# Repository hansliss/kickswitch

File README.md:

# kickswitch
Kickstart switcher for Amiga 2000

A switch for cramming 6 Kickstart images of different size into a single EPROM and make them switchable.

Switching is done by triggering a RESET low signal for at least two seconds, which can be done
from the keyboard by holding down CTRL-Amiga-Amiga.

Note that for some models of A500, you may need pullups on the address lines:
http://bax.comlab.uni-rostock.de/en/hardware/amiga500/kickstart-eprom/

A jumper is provided to select between pin 1 or 31 for A17 - older A2000 and A500 models
used the wrong pin for this.

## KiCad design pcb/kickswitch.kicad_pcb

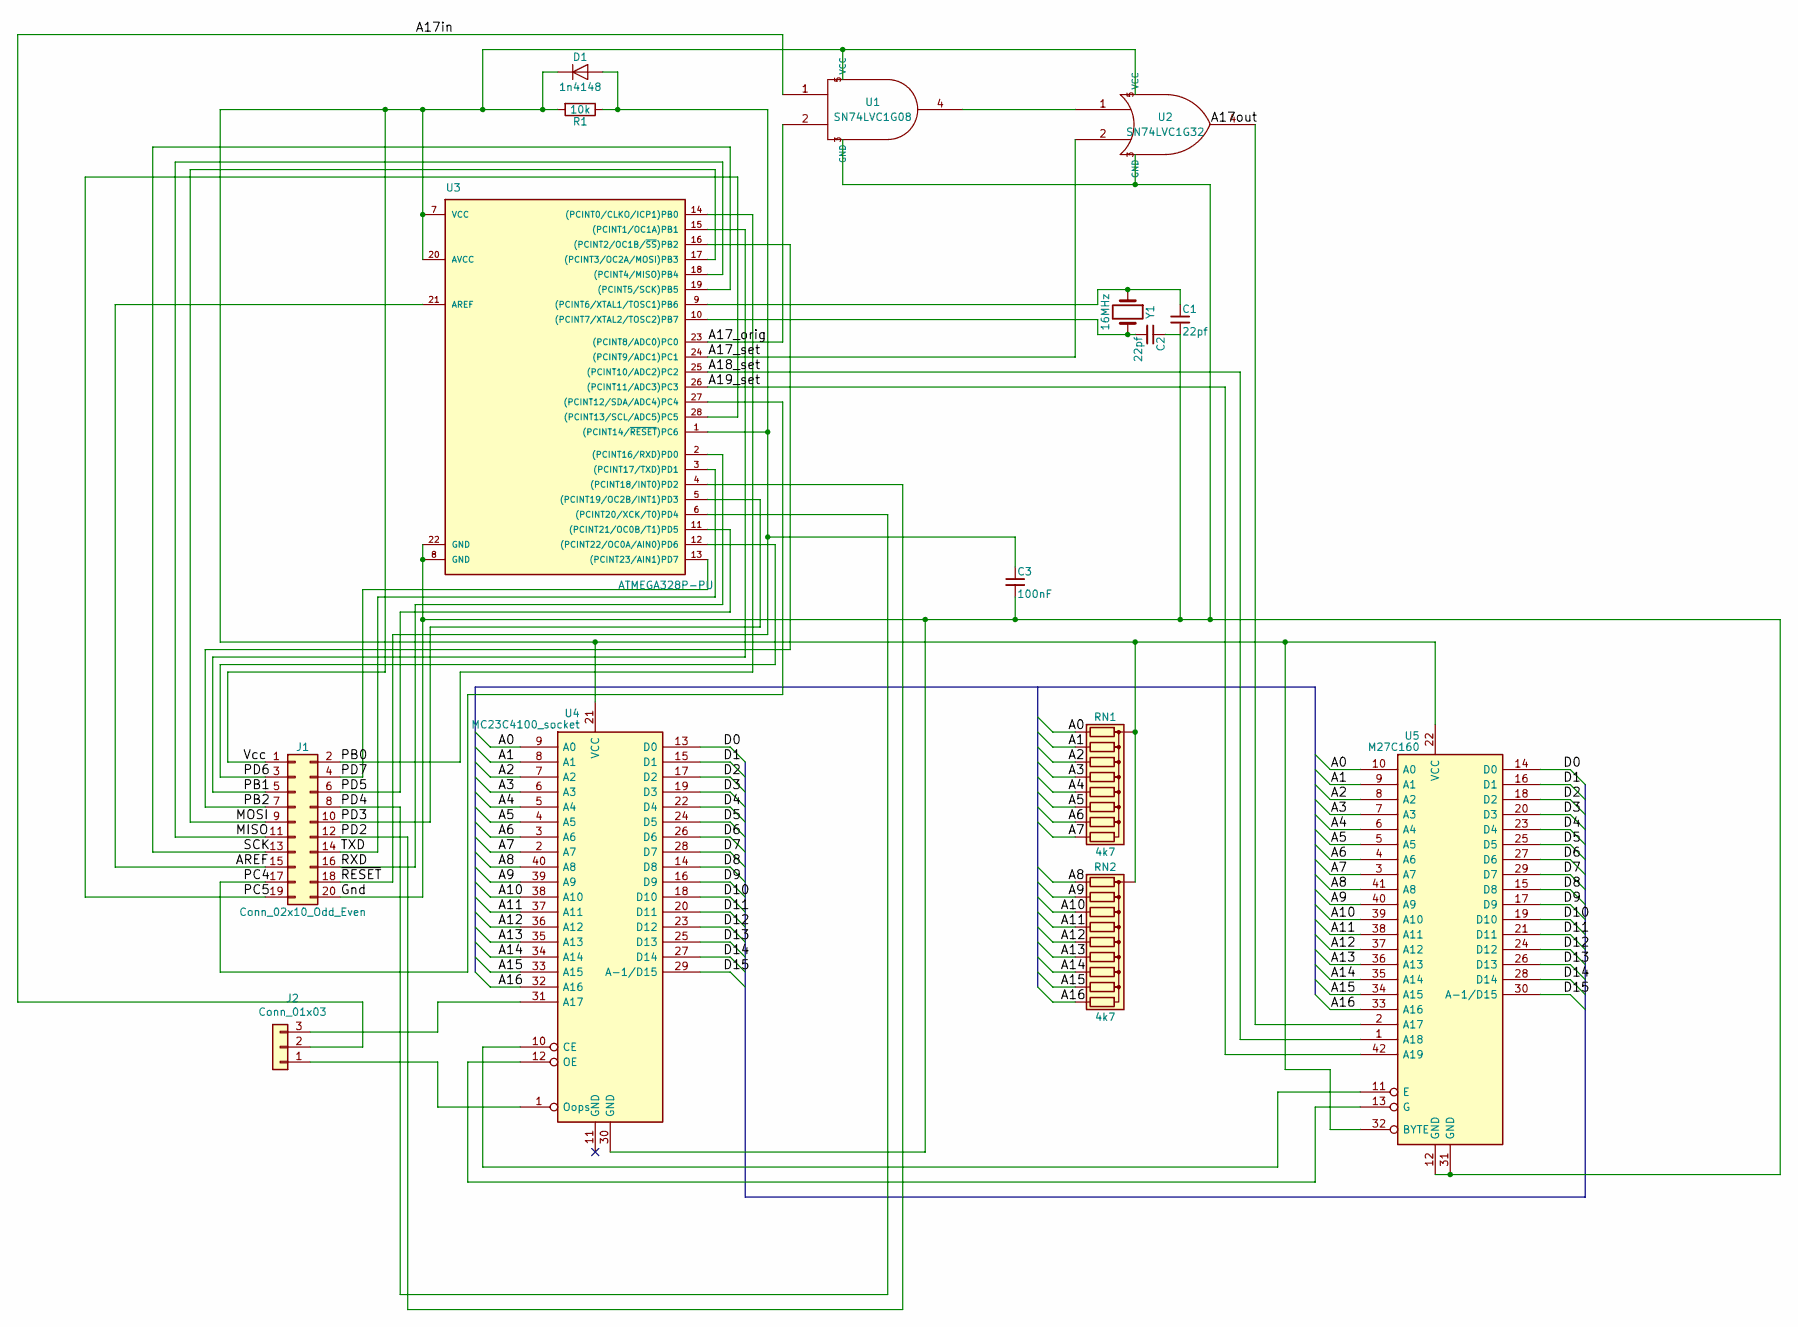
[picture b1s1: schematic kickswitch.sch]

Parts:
C1, C2: 22pf; C_0603
C3: 100nF; C_0603
D1: 1n4148; D_SOD-123F
J1: Conn_02x10_Odd_Even; Pin_Header_Straight_2x10_Pitch2.54mm
J2: Conn_01x03; Pin_Header_Straight_1x03_Pitch2.54mm
R1: 10k; R_0603
RN1: 4k7; R_Array_SIP9
RN2: 4k7; R_Array_SIP10
U1: SN74LVC1G08; SOT-23-5
U2: SN74LVC1G32; SOT-23-5
U3: ATMEGA328P-PU; DIP-28_W7.62mm
U4: MC23C4100_socket; DIP-40_W15.24mm_Socket
U5: M27C160; DIP-42_W15.24mm_Socket
Y1: 16MHz; Crystal_HC49-4H_Vertical

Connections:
/A0: RN1.2 (R1), U4.9 (A0), U5.10 (A0)
/A1: RN1.3 (R2), U4.8 (A1), U5.9 (A1)
/A2: RN1.4 (R3), U4.7 (A2), U5.8 (A2)
/A3: RN1.5 (R4), U4.6 (A3), U5.7 (A3)
/A4: RN1.6 (R5), U4.5 (A4), U5.6 (A4)
/A5: RN1.7 (R6), U4.4 (A5), U5.5 (A5)
/A6: RN1.8 (R7), U4.3 (A6), U5.4 (A6)
/A7: RN1.9 (R8), U4.2 (A7), U5.3 (A7)
/A8: RN2.2 (R1), U4.40 (A8), U5.41 (A8)
/A9: RN2.3 (R2), U4.39 (A9), U5.40 (A9)
/A10: RN2.4 (R3), U4.38 (A10), U5.39 (A10)
/A11: RN2.5 (R4), U4.37 (A11), U5.38 (A11)
/A12: RN2.6 (R5), U4.36 (A12), U5.37 (A12)
/A13: RN2.7 (R6), U4.35 (A13), U5.36 (A13)
/A14: RN2.8 (R7), U4.34 (A14), U5.35 (A14)
/A15: RN2.9 (R8), U4.33 (A15), U5.34 (A15)
/A16: RN2.10 (R9), U4.32 (A16), U5.33 (A16)
/A17_orig: U1.2, U3.23 ((PCINT8/ADC0)PC0)
/A17_set: U2.2, U3.24 ((PCINT9/ADC1)PC1)
/A17in: J2.2, U1.1
/A18_set: U3.25 ((PCINT10/ADC2)PC2), U5.1 (A18)
/A19_set: U3.26 ((PCINT11/ADC3)PC3), U5.42 (A19)
/AREF: J1.15, U3.21 (AREF)
/D0: U4.13 (D0), U5.14 (D0)
/D1: U4.15 (D1), U5.16 (D1)
/D2: U4.17 (D2), U5.18 (D2)
/D3: U4.19 (D3), U5.20 (D3)
/D4: U4.22 (D4), U5.23 (D4)
/D5: U4.24 (D5), U5.25 (D5)
/D6: U4.26 (D6), U5.27 (D6)
/D7: U4.28 (D7), U5.29 (D7)
/D8: U4.14 (D8), U5.15 (D8)
/D9: U4.16 (D9), U5.17 (D9)
/D10: U4.18 (D10), U5.19 (D10)
/D11: U4.20 (D11), U5.21 (D11)
/D12: U4.23 (D12), U5.24 (D12)
/D13: U4.25 (D13), U5.26 (D13)
/D14: U4.27 (D14), U5.28 (D14)
/D15: U4.29 (A-1/D15), U5.30 (A-1/D15)
/Gnd: C1.2, C2.1, C3.2, J1.20, U1.3 (GND), U2.3 (GND), U3.8 (GND), U3.22 (GND), U4.30 (GND), U5.12 (GND), U5.31 (GND)
/MISO: J1.11, U3.18 ((PCINT4/MISO)PB4)
/MOSI: J1.9, U3.17 ((PCINT3/OC2A/MOSI)PB3)
/PB0: J1.2, U3.14 ((PCINT0/CLKO/ICP1)PB0)
/PB1: J1.5, U3.15 ((PCINT1/OC1A)PB1)
/PB2: J1.7, U3.16 ((PCINT2/OC1B/~SS~)PB2)
/PC4: J1.17, U3.27 ((PCINT12/SDA/ADC4)PC4)
/PC5: J1.19, U3.28 ((PCINT13/SCL/ADC5)PC5)
/PD2: J1.12, U3.4 ((PCINT18/INT0)PD2)
/PD3: J1.10, U3.5 ((PCINT19/OC2B/INT1)PD3)
/PD4: J1.8, U3.6 ((PCINT20/XCK/T0)PD4)
/PD5: J1.6, U3.11 ((PCINT21/OC0B/T1)PD5)
/PD6: J1.3, U3.12 ((PCINT22/OC0A/AIN0)PD6)
/PD7: J1.4, U3.13 ((PCINT23/AIN1)PD7)
/RXD: J1.16, U3.2 ((PCINT16/RXD)PD0)
/SCK: J1.13, U3.19 ((PCINT5/SCK)PB5)
/TXD: J1.14, U3.3 ((PCINT17/TXD)PD1)
/Vcc: D1.1 (K), J1.1, R1.2, RN1.1 (common), RN2.1 (common), U1.5 (VCC), U2.5 (VCC), U3.7 (VCC), U3.20 (AVCC), U4.21 (VCC), U5.22 (VCC), U5.32 (BYTE)
/~RESET: C3.1, D1.2 (A), J1.18, R1.1, U3.1 ((PCINT14/~RESET~)PC6)
unnamed: C1.1, U3.9 ((PCINT6/XTAL1/TOSC1)PB6), Y1.1
unnamed: C2.2, U3.10 ((PCINT7/XTAL2/TOSC2)PB7), Y1.2
unnamed: J2.1, U4.1 (Oops)
unnamed: J2.3, U4.31 (A17)
unnamed: U1.4, U2.1
unnamed: U2.4, U5.2 (A17)
unnamed: U4.10 (CE), U5.11 (E)
unnamed: U4.12 (OE), U5.13 (G)

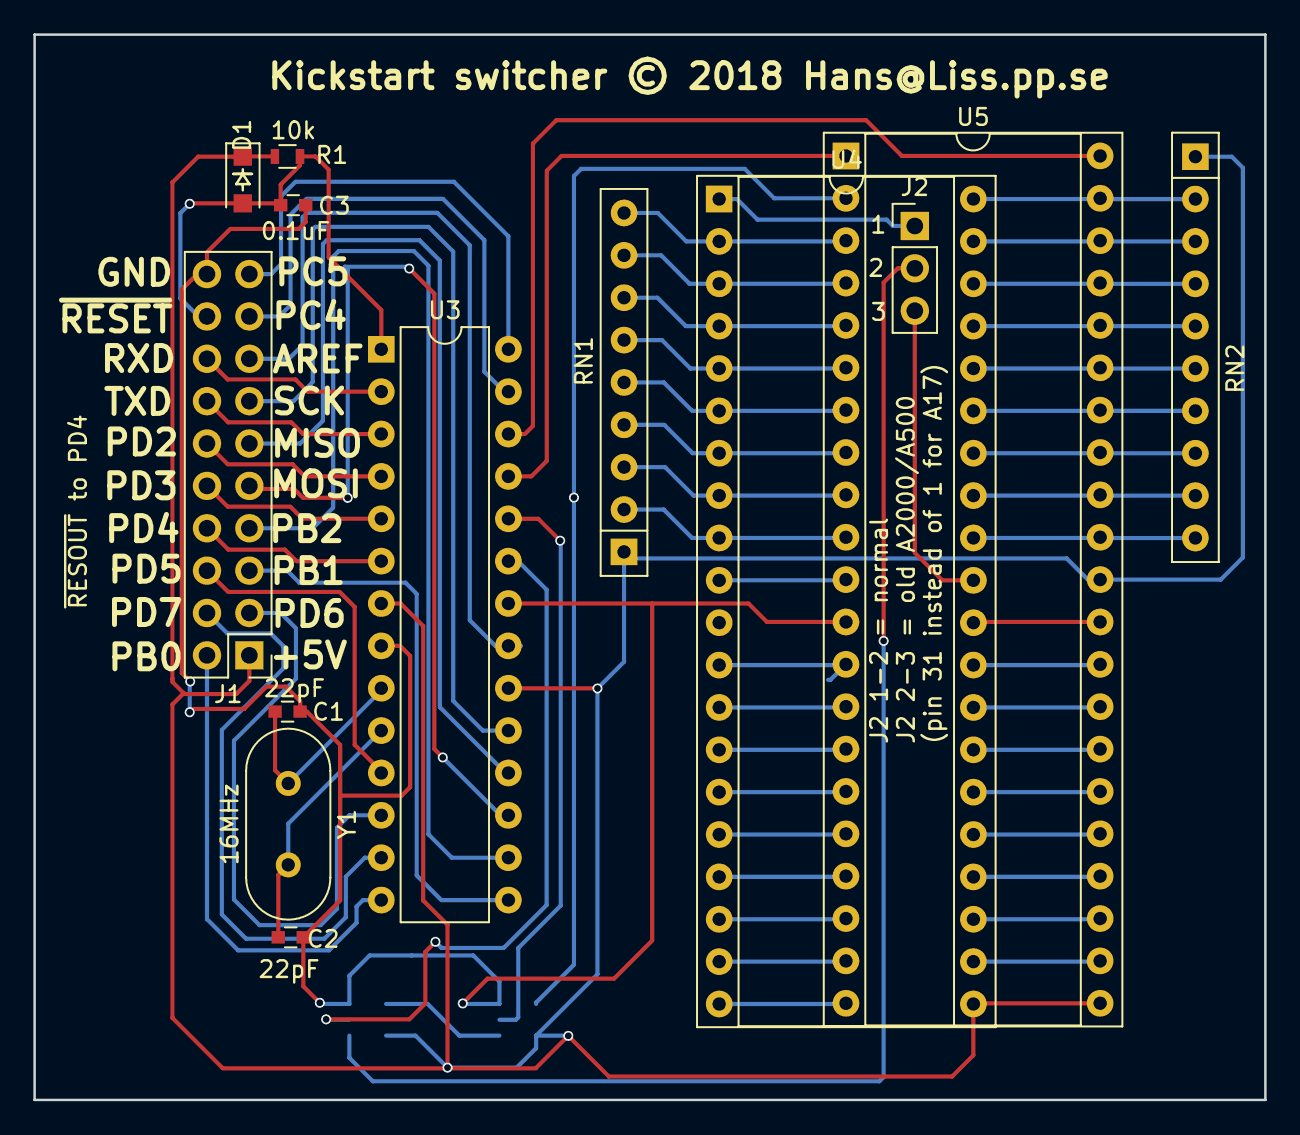
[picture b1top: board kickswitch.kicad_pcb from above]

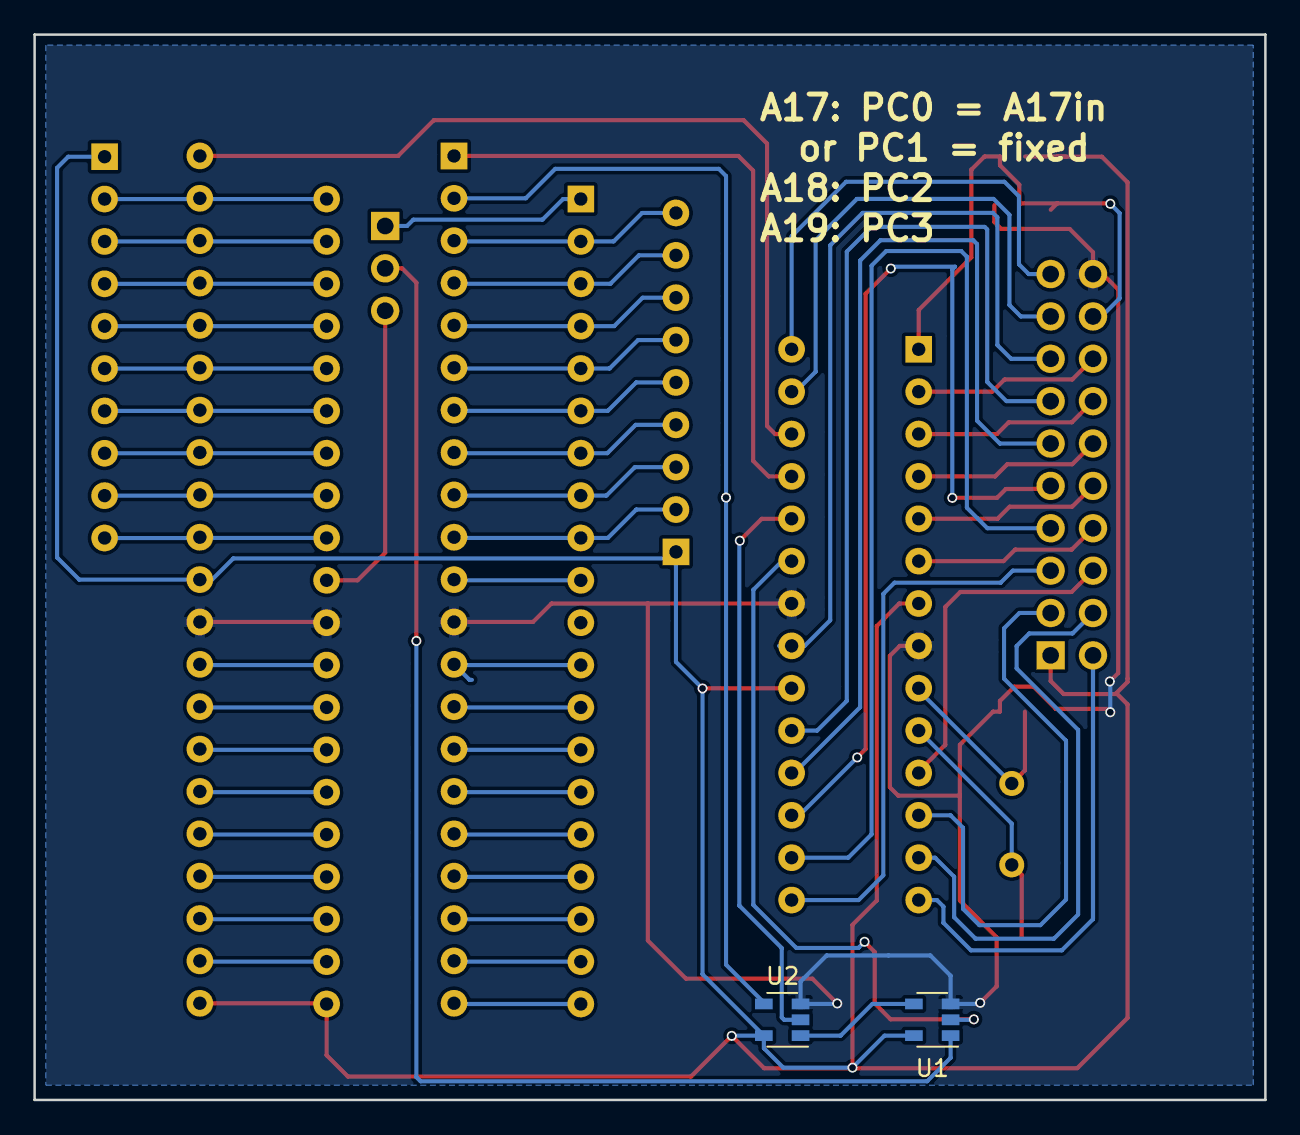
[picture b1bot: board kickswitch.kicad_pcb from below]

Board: 2 copper layers, 73.8 x 63.9 mm, 15 parts (2 on the bottom side), 66 nets.

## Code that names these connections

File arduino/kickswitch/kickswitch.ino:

/*
 * Kickswitch code
 * Produce adressing signals to a banked Kickstart ROM for A17 to A19 on PC0, PC1, PC2 and PC3 based on a selected value.
 * The value can be changed by holding a signal low for at least two seconds. This is intended to be taken from the
 * /RSTOUT signal on the parallel port on the Amiga, which will make it possible to switch between different Kickstart
 * versions by holding down CTRL-Amiga-Amiga for two seconds.
 * With six Kickstart images in a single ROM, the first four 128kW, and the last two 256kW, we need to be able to either
 * ignore the original A17 (for the first four) or use it (for the last two). The circuit will allow us to use PC0 to pass
 * through the original A17 to the ROM, or leave that off and use PC1 to set it HIGH/LOW. A18 and A19 are controlled by
 * PC2 and PC3, respectively. So we use a simple switch statement and set the appropriate values whenever the switch changes.
 */

#include <EEPROM.h>

#define RSTPin 4

int pc0 = 14;
int pc1 = 15;
int pc2 = 16;
int pc3 = 17;

int pinsByVal[] = {0x00, 0x02, 0x04, 0x06, 0x09, 0x0D};

int v;
int oldv;
int RSTState=HIGH;

void setup() {
  pinMode(pc0, OUTPUT);
  pinMode(pc1, OUTPUT);
  pinMode(pc2, OUTPUT);
  pinMode(pc3, OUTPUT);
  pinMode(RSTPin, INPUT_PULLUP);
  oldv = -1;
  v = EEPROM.read(0);
#ifdef SERIAL
  Serial.begin(9600);
#endif
}

long ResetMillis=-1;

void loop() {
  int curRSTState = digitalRead(RSTPin);
  if (curRSTState != RSTState) {
    if (curRSTState == LOW) {
      ResetMillis = millis();
    }
    RSTState = curRSTState;
  }
  if (RSTState == LOW && ResetMillis != -1) {
    long elapsed = millis() - ResetMillis;
    if (elapsed >= 2000) {
      v = (v + 1) % 6;
      ResetMillis = -1;
    }
  }
  if (v != oldv && RSTState == LOW) {
#ifdef SERIAL
    Serial.println(String(v) + ": " + String(pinsByVal[v]));
#endif
    oldv = v;
    EEPROM.write(0, v);
    digitalWrite(pc0, (pinsByVal[v] & 0x01)?HIGH:LOW);
    digitalWrite(pc1, (pinsByVal[v] & 0x02)?HIGH:LOW);
    digitalWrite(pc2, (pinsByVal[v] & 0x04)?HIGH:LOW);
    digitalWrite(pc3, (pinsByVal[v] & 0x08)?HIGH:LOW);
  }
  delay(200);
}

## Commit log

2018-06-22 Initial import
2018-06-22 Added NET file and component library
2018-06-22 Latest version. Added Arduino code
2018-06-22 Moved notes to separate file
2018-06-22 Added Gerber files
2018-07-05 Added many more I/O pins Removed reset button Added resistor nets for Address line pullups Added ground plane
2018-07-05 Added TODO note in Arduino code
2018-07-05 Added 8-to-3 encoder pcb
2018-07-05 Added power flags to encoder
2018-07-19 Added component list to notes.txt
2018-07-19 Added component list for encoder
2018-07-19 Updated component list in notes.txt
2018-07-29 Fixed bugs in new Arduino code after testing
2020-04-13 Upgraded to latest KiCAD. Eliminated encoder. Eliminated switch and added /RSTOUT input line instead. Added jumper for pin 1/31 "Oops" fix. Updated README.md.

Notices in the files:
pcb/kickswitch.kicad_pcb:
Kickstart switcher © 2018 Hans@Liss.pp.se
